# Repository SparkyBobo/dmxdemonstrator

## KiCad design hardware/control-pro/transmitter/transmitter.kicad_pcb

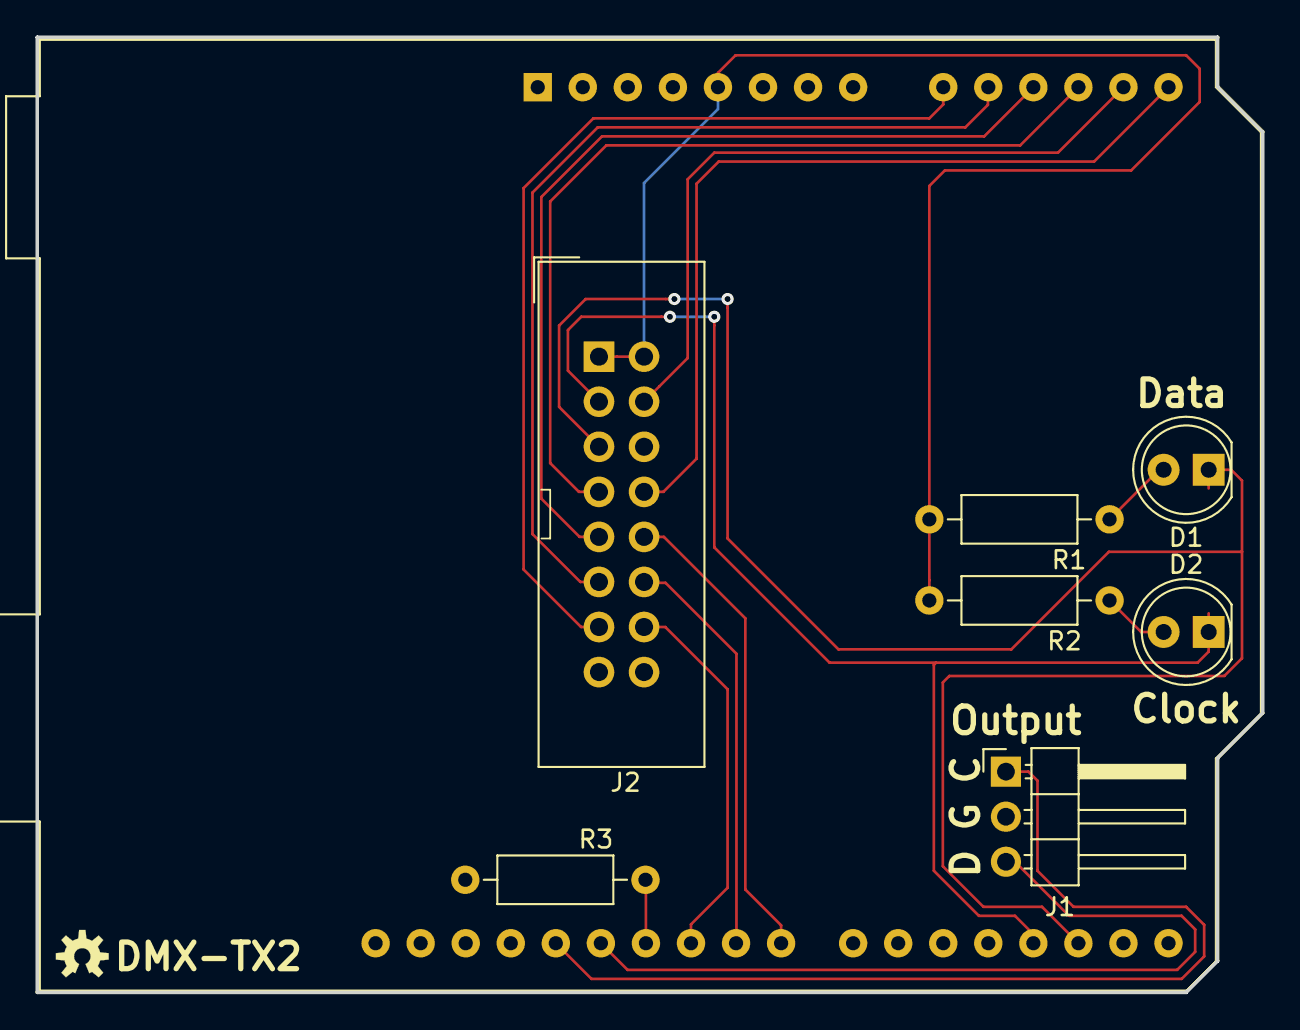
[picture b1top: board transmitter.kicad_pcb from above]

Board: 2 copper layers, 69.1 x 53.8 mm, 8 parts (0 on the bottom side), 18 nets.

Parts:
A1: Arduino_UNO_R3
D1: DATA; LED_D5.0mm
D2: CLOCK; LED_D5.0mm
J1: Output; PinHeader_1x03_P2.54mm_Horizontal
J2: INPUT; IDC-Header_2x08_P2.54mm_Vertical
R1, R2, R3: 330; R_Axial_DIN0207_L6.3mm_D2.5mm_P10.16mm_Horizontal

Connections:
+5V: A1.5, J2.1, J2.2, R1.1, R2.1
/A0: A1.9, J2.13
/A1: A1.10, J2.11
/A2: A1.11, J2.9
/A3: A1.12, J2.7
/A4: A1.13, J2.4
/A5: A1.14, J2.8
/RX: A1.27, J1.3
/RXCLK: A1.28, J1.1
/~CLK_FST: A1.24, J2.12
/~CLK_SLO: A1.23, J2.10
/~CLOCK: A1.18, D2.1, J2.3
/~DATA: A1.17, D1.1, J2.5
/~HWD_DT: A1.25, J2.14
GND: A1.6, A1.7, A1.29, J1.2, J2.6, J2.15, J2.16, R3.2
unnamed: A1.26, R3.1
unnamed: D1.2, R1.2
unnamed: D2.2, R2.2

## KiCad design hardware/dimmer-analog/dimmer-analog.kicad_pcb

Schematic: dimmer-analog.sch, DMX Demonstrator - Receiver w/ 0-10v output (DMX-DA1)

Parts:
A1: Arduino_UNO_R3
C1, C2, C3, C4: .01uF; CAP-PTH-2.54
C5: 10uF; CP_Radial_D5.0mm_P2.50mm
D1: DATA; LED_D5.0mm
D2: CLOCK; LED_D5.0mm
D8: 1N5819; D_DO-41_SOD81_P10.16mm_Horizontal
J1: Input; PinHeader_1x03_P2.54mm_Horizontal
J2: DIMMER_B; PhoenixContact_MSTBA_2,5_5-G-5,08_1x05_P5.08mm_Horizontal
J5: 12V_A; BarrelJack_CUI_PJ-063AH_Horizontal
J6: 12V_B; PhoenixContact_MSTBA_2,5_2-G-5,08_1x02_P5.08mm_Horizontal
R1, R2: 330; R_Axial_DIN0207_L6.3mm_D2.5mm_P10.16mm_Horizontal
R7: 390; R_Axial_DIN0207_L6.3mm_D2.5mm_P10.16mm_Horizontal
R8: 2.7k; R_Axial_DIN0207_L6.3mm_D2.5mm_P10.16mm_Horizontal
U1: LM317T; TO-220-3_Horizontal_TabDown; MPN LM317T; Digi-Key_PN 497-1575-5-ND
U2: 74LS164; DIP-14_W7.62mm
U3: TLC7226A; DIP-20_W7.62mm
U4: LM324A; DIP-14_W7.62mm

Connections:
+5V: A1.5, C2.1, C3.1, R1.1, R2.1, U2.1, U2.14, U3.18
+10V: C1.1, C4.1, C5.1, R7.2, U1.2, U3.4, U4.4 (V+)
/A0: A1.9, U3.17
/A1: A1.10, U3.16
/AO0: U3.2, U4.12 (+)
/AO1: U3.1, U4.3 (+)
/AO2: U3.20, U4.5 (+)
/AO3: U3.19, U4.10 (+)
/B: A1.22, U2.2
/CLK: A1.23, U2.8
/RX: A1.27, J1.3
/RXCLK: A1.28, J1.1
/~CLOCK: A1.14, D2.1
/~CLR: A1.24, U2.9
/~DATA: A1.13, D1.1
/~DIM0: A1.26
/~DIM1: A1.25
/~DIM2: A1.21
/~DIM3: A1.20
/~WR: A1.11, U3.15
GND: A1.6, A1.7, A1.29, C1.2, C2.2, C3.2, C4.2, C5.2, J1.2, J2.1, J5.2, J6.1, R8.1, U2.7, U3.3, U3.5, U3.6, U4.11 (V-)
unnamed: D1.2, R1.2
unnamed: D2.2, R2.2
unnamed: D8.1 (K), U1.3
unnamed: D8.2 (A), J5.1, J6.2
unnamed: J2.2, U4.13 (-), U4.14
unnamed: J2.3, U4.1, U4.2 (-)
unnamed: J2.4, U4.6 (-), U4.7
unnamed: J2.5, U4.8, U4.9 (-)
unnamed: R7.1, R8.2, U1.1
unnamed: U2.3, U3.14
unnamed: U2.4, U3.13
unnamed: U2.5, U3.12
unnamed: U2.6, U3.11
unnamed: U2.10, U3.10
unnamed: U2.11, U3.9
unnamed: U2.12, U3.8
unnamed: U2.13, U3.7

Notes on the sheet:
D0-D4 Reserved For DMX Shield

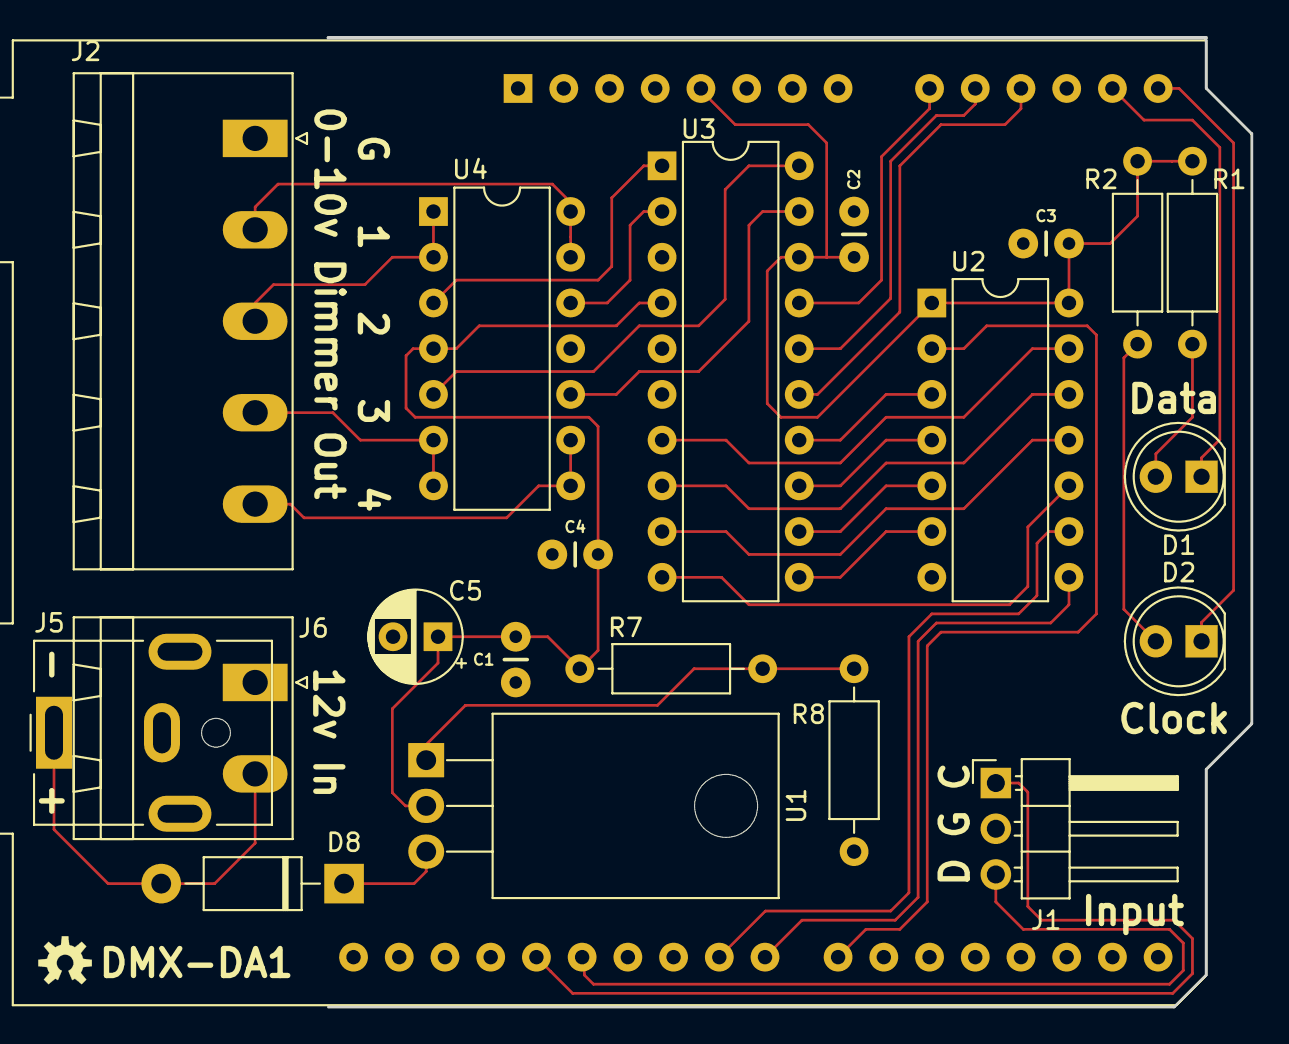
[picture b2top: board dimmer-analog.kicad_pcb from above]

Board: 2 copper layers, 51.3 x 53.8 mm, 21 parts (0 on the bottom side), 34 nets.

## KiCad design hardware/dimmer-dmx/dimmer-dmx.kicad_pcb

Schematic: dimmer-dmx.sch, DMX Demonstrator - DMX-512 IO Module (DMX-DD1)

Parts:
C2, C3, C4, C5: .01uF; CAP-PTH-2.54
J1: IO EXTENSION; IDC-Header_2x07_P2.54mm_Horizontal
J2: NC3FAH/NC5FAH; NEUTRIK-NC3FAH-NC5FAH
J3: NC3MAH/NC5MAH; NEUTRIK-NC3MAH-NC5MAH
MH1, MH2, MH3, MH4: MountingHole; MountingHole_3.2mm_M3
R1: 330; R_Axial_DIN0207_L6.3mm_D2.5mm_P10.16mm_Horizontal
R2, R3, R4, R5, R6, R7: 470; R_Axial_DIN0207_L6.3mm_D2.5mm_P10.16mm_Horizontal
R8, R10: 680; R_Axial_DIN0207_L6.3mm_D2.5mm_P10.16mm_Horizontal
R9: 120; R_Axial_DIN0207_L6.3mm_D2.5mm_P10.16mm_Horizontal
U1: NMA0505SC; Converter_DCDC_muRata_NMAxxxxSC_THT_Bypass
U2, U3, U4: 6N137; DIP-8_W7.62mm_Socket; MPN 6N137; Digi-Key_PN 160-1791-ND
U5: MAX3485CPA+; DIP-8_W7.62mm_Socket

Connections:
+5V: C2.1, J1.1, J1.2, R2.1, U1.1 (VIN+), U2.8, U3.2, U4.2
GND: C2.2, J1.13, J1.14, R1.1, U1.2 (VIN-), U2.5
GNDD: C3.2, C4.2, C5.2, J2.1A, J2.1B, J3.1A, J3.1B, R10.2, U1.4 (VOUT-), U3.5, U4.5, U5.5 (GND)
unnamed: J1.9, R2.2, U2.6
unnamed: J1.10, R4.2
unnamed: J1.11, R6.2
unnamed: J1.12, R1.2
unnamed: J2.2A, J2.2B, J3.2A, J3.2B, R9.1, R10.1, U5.7 (B)
unnamed: J2.3, J3.3, R8.1, R9.2, U5.6 (A)
unnamed: R3.1, U5.1 (RO)
unnamed: R3.2, U2.3
unnamed: R4.1, U3.3
unnamed: R5.1, U3.6, U5.2 (~RE), U5.3 (DE)
unnamed: R6.1, U4.3
unnamed: R7.1, U4.6, U5.4 (DI)
VDD: C3.1, C4.1, C5.1, R5.2, R7.2, R8.2, U1.6 (VOUT+), U2.2, U3.8, U4.8, U5.8 (VCC)

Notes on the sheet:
Connect pin 3 to 6 to bypass isolator
Connect J4 to J5 to bypass isolator
Connect pin 2 to 4 to bypass isolator

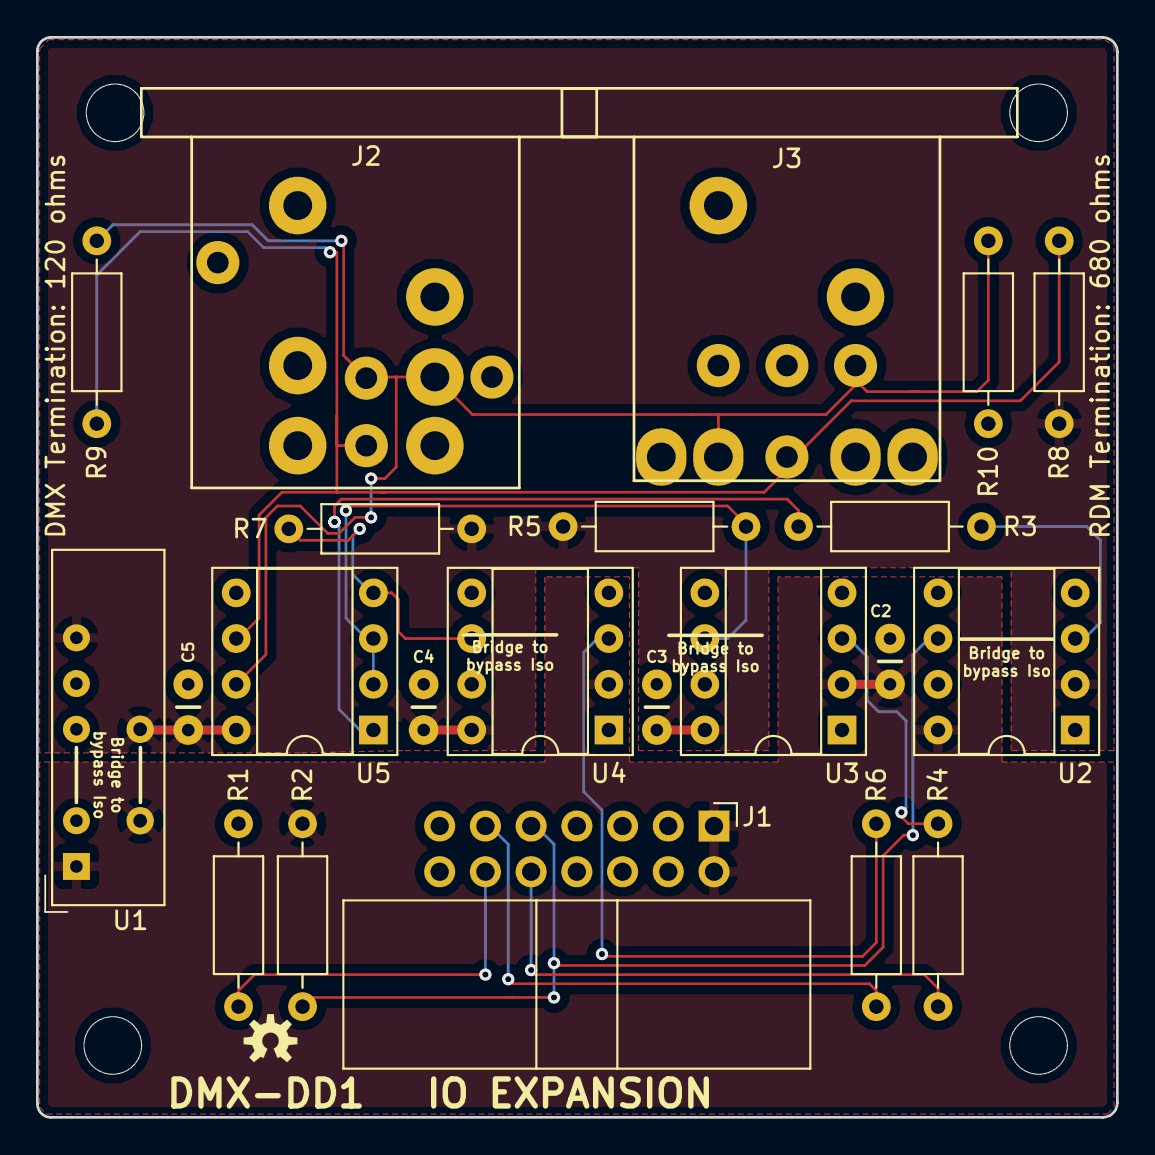
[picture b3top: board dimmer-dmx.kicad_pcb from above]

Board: 2 copper layers, 60.0 x 60.0 mm, 26 parts (0 on the bottom side), 16 nets.

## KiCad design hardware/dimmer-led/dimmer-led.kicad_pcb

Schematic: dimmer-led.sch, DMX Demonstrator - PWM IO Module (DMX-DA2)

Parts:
C1, C2, C3, C4: .01uF; CAP-PTH-2.54
C5: 10uF; CP_Radial_D5.0mm_P2.50mm
C6, C8, C9: 10nf; CAP-PTH-2.54
C7: 100nf; CAP-PTH-2.54
D8: 1N5819; D_DO-41_SOD81_P10.16mm_Horizontal
J1: IO EXTENSION; IDC-Header_2x07_P2.54mm_Horizontal
J2: PWM_OUT; PhoenixContact_MSTBA_2,5_5-G-5,08_1x05_P5.08mm_Horizontal
J5: 12V_A; BarrelJack_CUI_PJ-063AH_Horizontal
J6: 12V_B; PhoenixContact_MSTBA_2,5_2-G-5,08_1x02_P5.08mm_Horizontal
MH1, MH2, MH3, MH4: MountingHole; MountingHole_3.2mm_M3
R1: 10k; R_Axial_DIN0207_L6.3mm_D2.5mm_P10.16mm_Horizontal
R2, R3: 1k; R_Axial_DIN0207_L6.3mm_D2.5mm_P10.16mm_Horizontal
R7: 390; R_Axial_DIN0207_L6.3mm_D2.5mm_P10.16mm_Horizontal
R8: 2.7k; R_Axial_DIN0207_L6.3mm_D2.5mm_P10.16mm_Horizontal
U1: LM317T; TO-220-3_Horizontal_TabDown; MPN LM317T; Digi-Key_PN 497-1575-5-ND
U2: 74LS164; DIP-14_W7.62mm
U3: TLC7226A; DIP-20_W7.62mm
U4: LM339; DIP-14_W7.62mm
U5: LM555; DIP-8_W7.62mm

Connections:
+5V: C2.1, C3.1, J1.1, J1.2, U2.1, U2.14, U3.18
+10V: C1.1, C4.1, C5.1, R7.2, U1.2, U3.4, U4.3 (V+), U5.4, U5.8
/A0: J1.5, U3.17
/A1: J1.7, U3.16
/AO0: U3.2, U4.9 (+)
/AO1: U3.1, U4.5 (+)
/AO2: U3.20, U4.7 (+)
/AO3: U3.19, U4.11 (+)
/~WR: J1.3, U3.15
GND: C1.2, C2.2, C3.2, C4.2, C5.2, C6.1, C7.1, C8.2, C9.2, J1.13, J1.14, J2.1, J5.2, J6.1, R8.1, U2.7, U3.3, U3.5, U3.6, U4.12 (V-), U5.1
unnamed: C6.2, U5.2
unnamed: C7.2, U5.5
unnamed: C8.1, R2.1, R3.2
unnamed: C9.1, R3.1, U4.4 (-), U4.6 (-), U4.8 (-), U4.10 (-)
unnamed: D8.1 (K), U1.3
unnamed: D8.2 (A), J5.1, J6.2
unnamed: J1.4, U2.2
unnamed: J1.6, U2.8
unnamed: J1.8, U2.9
unnamed: J2.2, U4.14
unnamed: J2.3, U4.2
unnamed: J2.4, U4.1
unnamed: J2.5, U4.13
unnamed: R1.1, U5.6
unnamed: R1.2, R2.2, U5.3
unnamed: R7.1, R8.2, U1.1
unnamed: U2.3, U3.14
unnamed: U2.4, U3.13
unnamed: U2.5, U3.12
unnamed: U2.6, U3.11
unnamed: U2.10, U3.10
unnamed: U2.11, U3.9
unnamed: U2.12, U3.8
unnamed: U2.13, U3.7

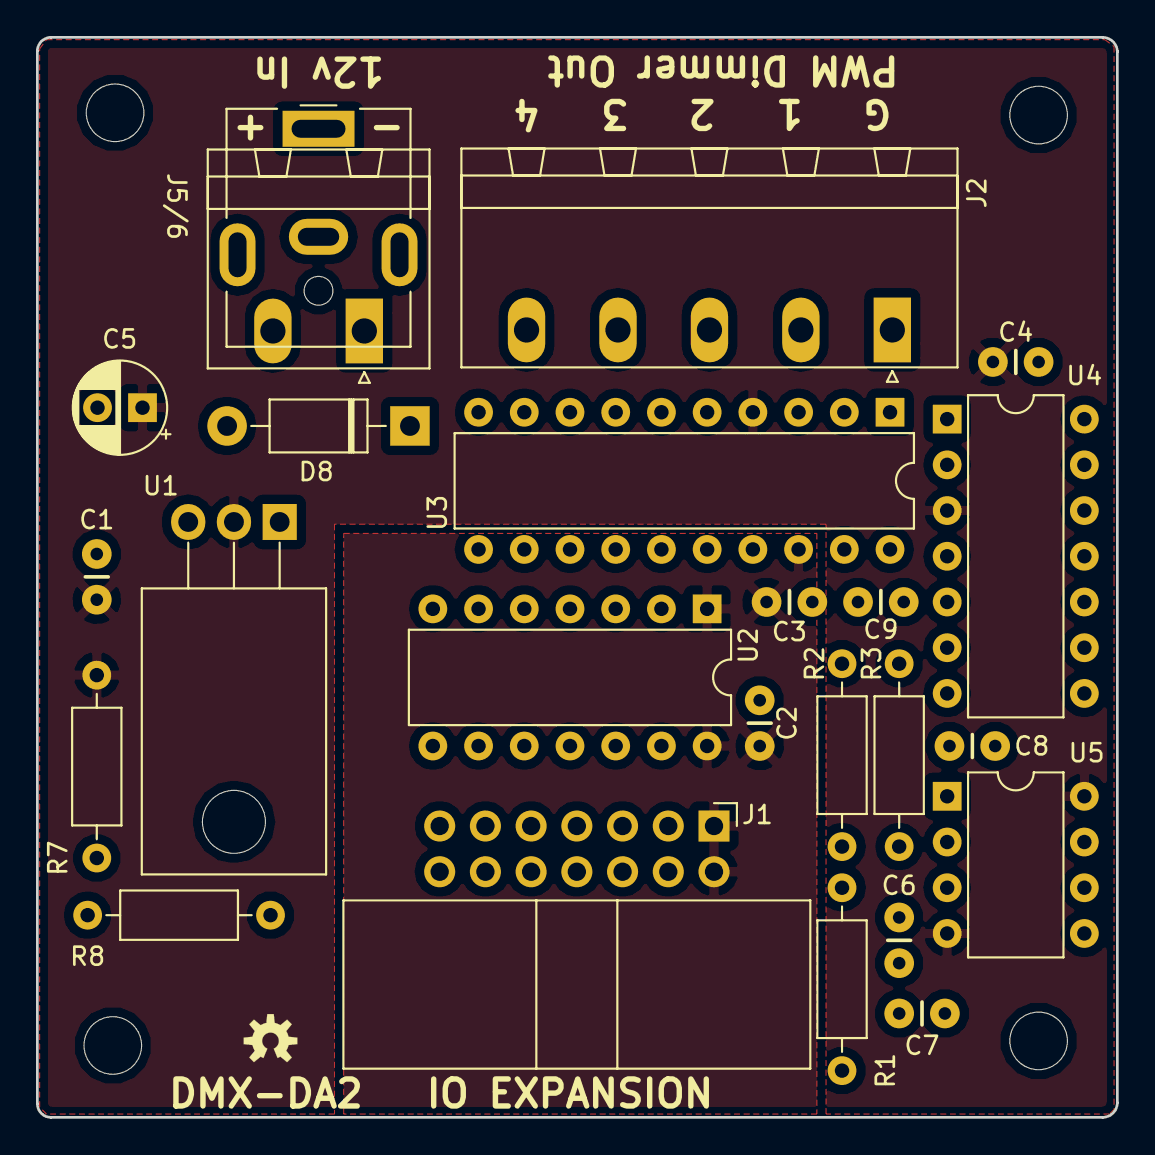
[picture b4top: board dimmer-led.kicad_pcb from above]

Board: 2 copper layers, 60.0 x 60.0 mm, 28 parts (0 on the bottom side), 34 nets, no tracks yet.

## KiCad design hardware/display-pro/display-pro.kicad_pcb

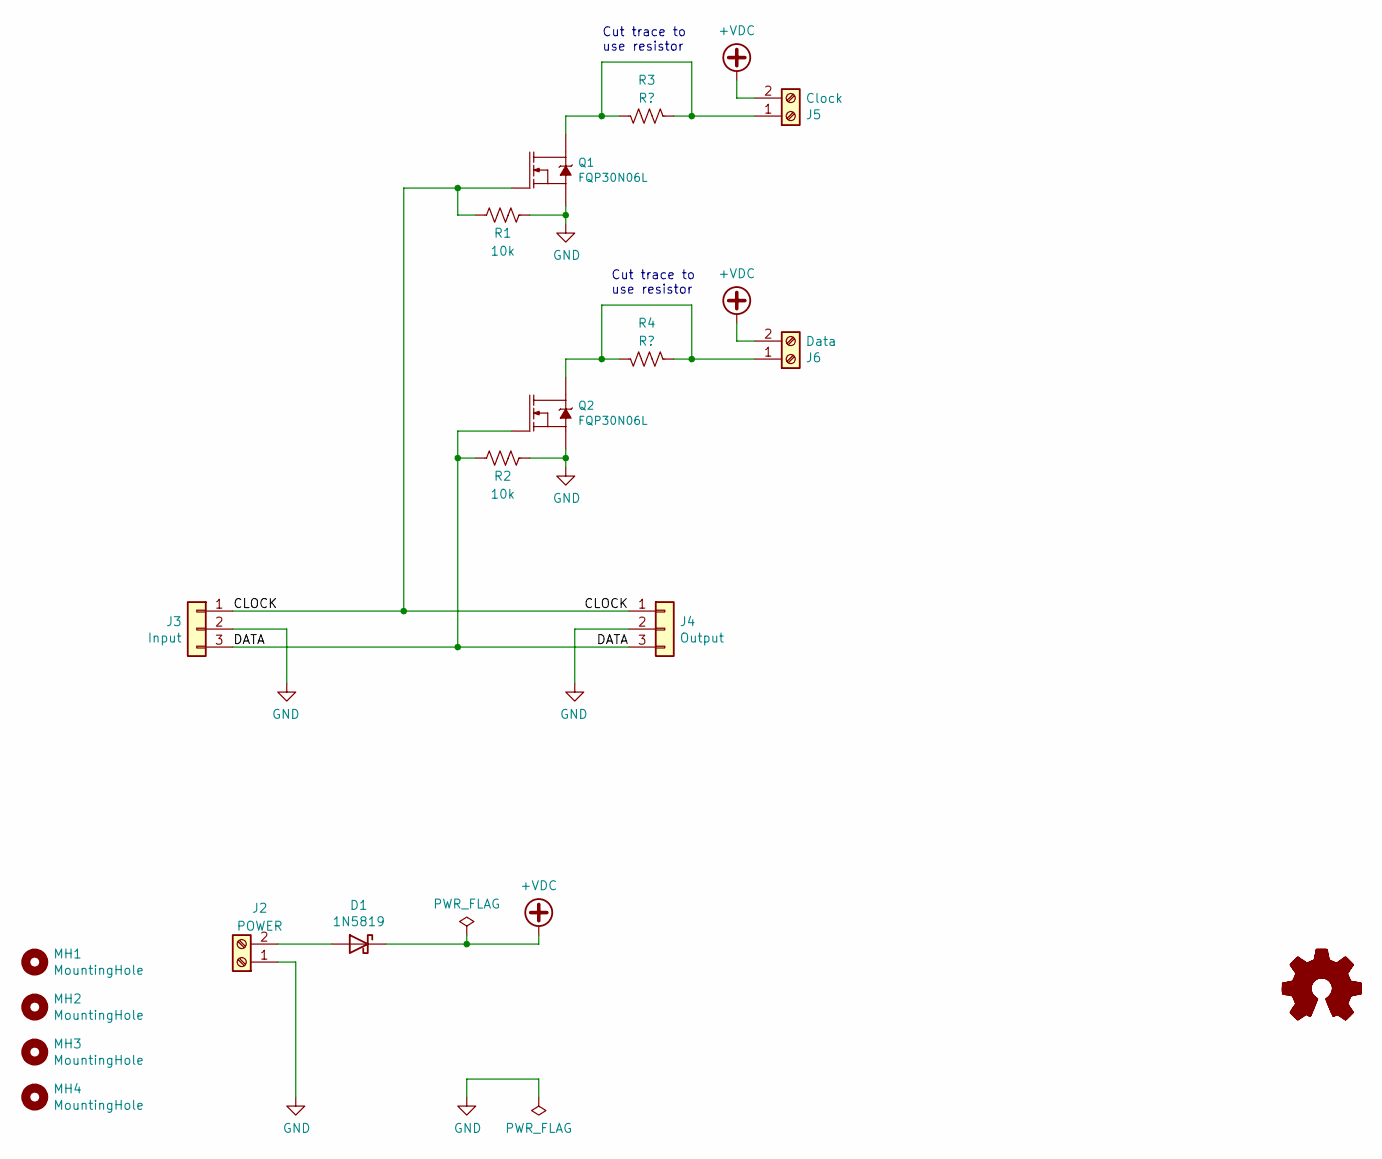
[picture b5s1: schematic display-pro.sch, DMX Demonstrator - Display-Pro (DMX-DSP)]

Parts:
D1: 1N5819; D_DO-41_SOD81_P10.16mm_Horizontal
J2: POWER; PhoenixContact_MSTBA_2,5_2-G-5,08_1x02_P5.08mm_Horizontal
J3: Input; PinHeader_1x03_P2.54mm_Horizontal
J4: Output; PinHeader_1x03_P2.54mm_Horizontal
J5: Clock; PhoenixContact_MSTBA_2,5_2-G-5,08_1x02_P5.08mm_Horizontal
J6: Data; PhoenixContact_MSTBA_2,5_2-G-5,08_1x02_P5.08mm_Horizontal
MH1, MH2, MH3, MH4: MountingHole; MountingHole_3.2mm_M3
Q1, Q2: FQP30N06L; TO-220-3_Horizontal_TabDown
R1, R2: 10k; R_Axial_DIN0207_L6.3mm_D2.5mm_P10.16mm_Horizontal
R3, R4: R?; R_Axial_DIN0411_L9.9mm_D3.6mm_P15.24mm_Horizontal

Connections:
+VDC: D1.1 (K), J5.2, J6.2
/CLOCK: J3.1, J4.1, Q1.1 (G), R1.2
/DATA: J3.3, J4.3, Q2.1 (G), R2.2
GND: J2.1, J3.2, J4.2, Q1.3 (S), Q2.3 (S), R1.1, R2.1
unnamed: D1.2 (A), J2.2
unnamed: J5.1, Q1.2 (D), R3.1, R3.2
unnamed: J6.1, Q2.2 (D), R4.1, R4.2

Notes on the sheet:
Cut trace to use resistor

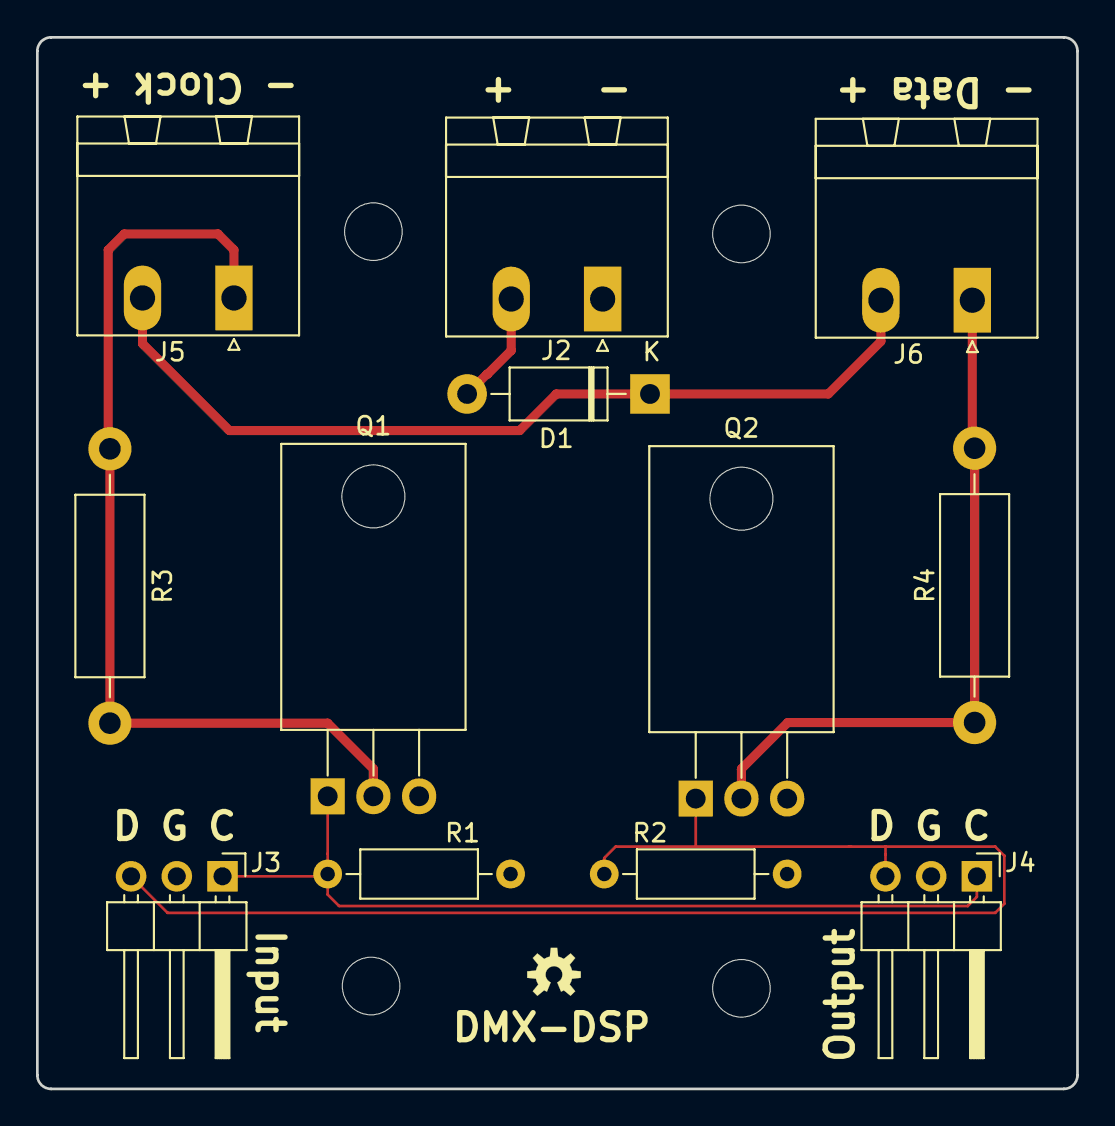
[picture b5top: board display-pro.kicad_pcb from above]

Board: 2 copper layers, 57.8 x 58.4 mm, 16 parts (0 on the bottom side), 7 nets.

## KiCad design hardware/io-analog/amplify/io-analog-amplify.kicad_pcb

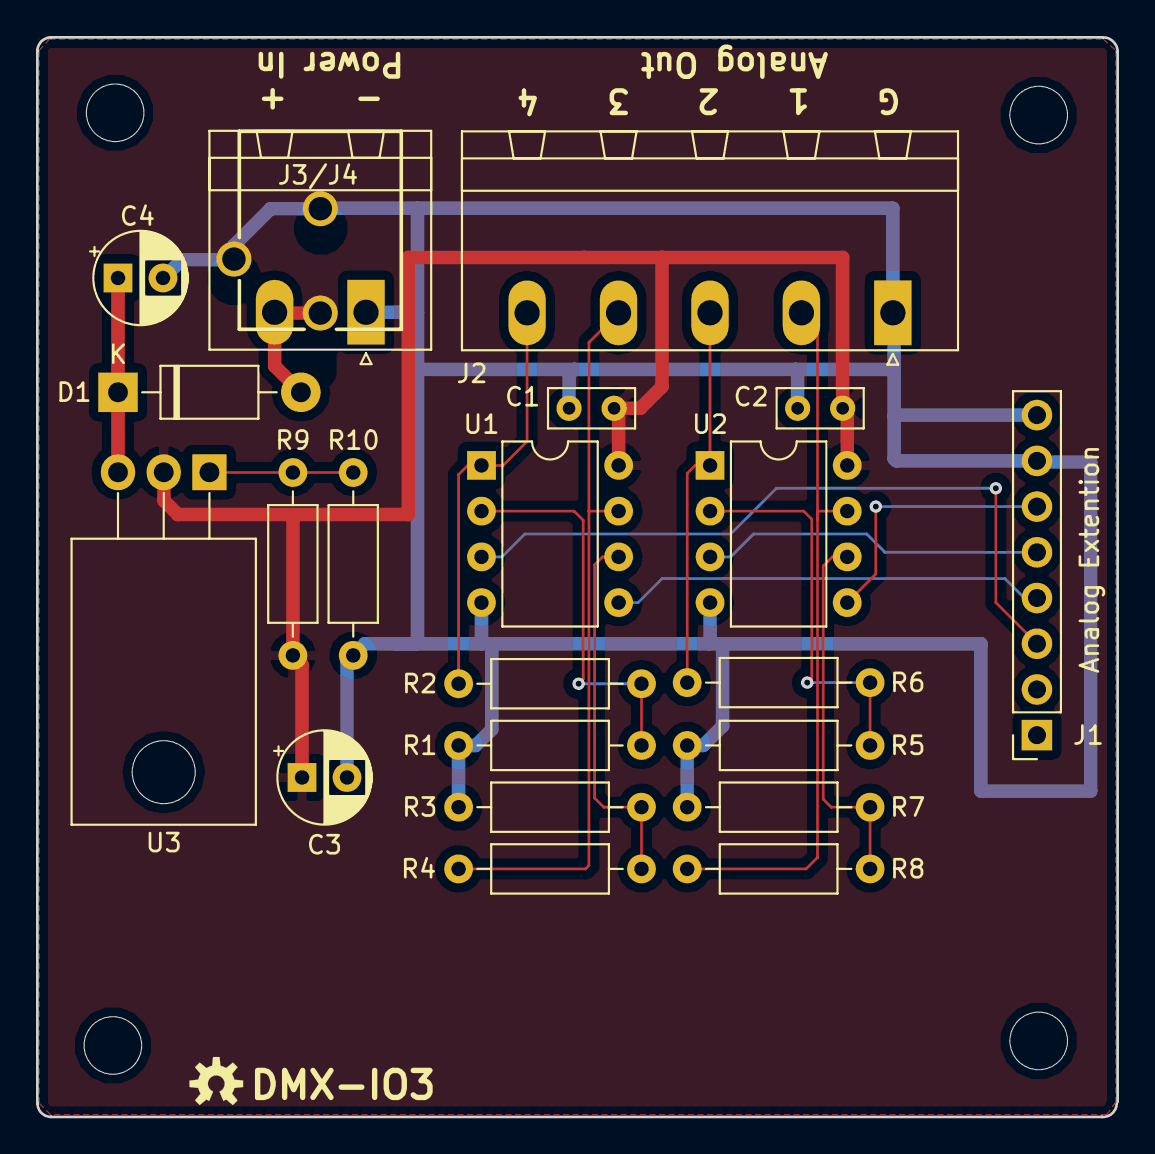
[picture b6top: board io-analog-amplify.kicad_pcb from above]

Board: 2 copper layers, 60.0 x 60.0 mm, 26 parts (0 on the bottom side), 17 nets.

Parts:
C1, C2: 0.1uF; C_Rect_L4.6mm_W2.0mm_P2.50mm_MKS02_FKP02
C3, C4: 10uF; CP_Radial_D5.0mm_P2.50mm
D1: 1N5819; D_DO-41_SOD81_P10.16mm_Horizontal
J1: Analog Extension; PinSocket_1x08_P2.54mm_Vertical
J2: Output; PhoenixContact_MSTBA_2,5_5-G-5,08_1x05_P5.08mm_Horizontal
J3: Power; PhoenixContact_MSTBA_2,5_2-G-5,08_1x02_P5.08mm_Horizontal
J4: Power; POWER_JACK_PTH_BREAD
MH1, MH2, MH3, MH4: MountingHole; MountingHole_3.2mm_M3
R1, R3, R5, R7: 22.6k 1%; R_Axial_DIN0207_L6.3mm_D2.5mm_P10.16mm_Horizontal
R2, R4, R6, R8: 68.1k 1%; R_Axial_DIN0207_L6.3mm_D2.5mm_P10.16mm_Horizontal
R9: 392 1%; R_Axial_DIN0207_L6.3mm_D2.5mm_P10.16mm_Horizontal
R10: 2.74k 1%; R_Axial_DIN0207_L6.3mm_D2.5mm_P10.16mm_Horizontal
U1, U2: TLV2772; DIP-8_W7.62mm
U3: LM317T; TO-220-3_Horizontal_TabDown

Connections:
/AO0: J1.6, U2.5
/AO1: J1.5, U2.3
/AO2: J1.4, U1.5
/AO3: J1.3, U1.3
GND: C1.2, C2.2, C3.2, C4.2, J1.7, J1.8, J2.1, J3.1, J4.GND, J4.GNDB, R1.1, R3.1, R5.1, R7.1, R10.1, U1.4, U2.4
unnamed: C1.1, C2.1, C3.1, R9.2, U1.8, U2.8, U3.2
unnamed: C4.1, D1.1, U3.3
unnamed: D1.2, J3.2, J4.PWR
unnamed: J2.2, R8.2, U2.7
unnamed: J2.3, R6.2, U2.1
unnamed: J2.4, R4.2, U1.7
unnamed: J2.5, R2.1, U1.1
unnamed: R1.2, R2.2, U1.2
unnamed: R3.2, R4.1, U1.6
unnamed: R5.2, R6.1, U2.2
unnamed: R7.2, R8.1, U2.6
unnamed: R9.1, R10.2, U3.1

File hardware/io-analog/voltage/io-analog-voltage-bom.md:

# Bill Of Materials (BOM)

## Schematic

**Filename:** E:\OpenSource\dmxdemonstrator\hardware\io-analog\voltage\io-analog-voltage.sch

**Date Modified:** 8/20/2023 10:47:27 PM

**Kicad Version:** Eeschema (5.0.0)

**Component Count:** 26

## Parts

Reference|Quantity|Value|Part|Datasheet|Vendor(s)
---------|--------|-----|----|---------|------
C1, C2|2|0.1uF|Decoupling Capacitor|~|[Mouser 80-C320C104K5R7301](https://www.mouser.com/ProductDetail/KEMET/C320C104K5R5TA730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, [Newark 13K6284](https://www.newark.com/kemet/c315c104m5u5ta/capacitor-mlcc-z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, [Sparkfun COM-08375](https://www.sparkfun.com/products/8375), [Adafruit 753](https://www.adafruit.com/product/753)
C3, C4|2|10uF|Filter Capacitor|~|[Digikey P10425CT-ND](https://www.digikey.com/en/products/detail/panasonic-electro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, [Mouser 667-ECA-1HM100I](https://www.mouser.com/ProductDetail/Panasonic/ECA-1HM100I), [Newark ECA-1HM100I](), [Sparkfun COM-00523](https://www.sparkfun.com/products/523), [Adafruit 2195](https://www.adafruit.com/product/2195)
D1|1|1N5819|Reverse Voltage Protection|[Data Sheet](http://www.vishay.com/docs/88525/1n5817.pdf)|[Digikey 1N5819-E3/54GITR-ND](https://www.digikey.com/en/products/detail/vishay-general-se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, [Mouser 625-1N5819-E3](https://www.mouser.com/ProductDetail/Vishay-General-Semicond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, [Newark 78K2616](https://www.newark.com/vishay/1n5819-e3-54/schottky-rectifie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, [Sparkfun COM-10926](https://www.sparkfun.com/products/10926)
J1|1|Analog Extension|Arduino Stackable Header - 8 Pin|~|[Mouser 992-8FX1L-254MM](https://www.mouser.com/ProductDetail/Gravitech/8Fx1L-254mm?q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, [Sparkfun PRT-09279](https://www.sparkfun.com/products/9279)
J2|1|Output|Screw Terminal|~|[Digikey 277-1109-ND](https://www.digikey.com/en/products/detail/phoenix-contact/1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, [Mouser 651-1757271](https://www.mouser.com/ProductDetail/Phoenix-Contact/1757271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
J3|1|Power|Screw Terminal|~|[Digikey 277-1106-ND](https://www.digikey.com/en/products/detail/phoenix-contact/1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, [Mouser 651-1757242](https://www.mouser.com/ProductDetail/Phoenix-Contact/1757242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
J4|1|Power|DC Barrel Jack|[Data Sheet](https://www.sparkfun.com/products/10811)|[Sparkfun CONN-08197](https://www.sparkfun.com/products/10811)
R1, R3, R5, R7|4|22.6k 1%||~|[Digikey 22.6KXBK-ND](https://www.digikey.com/en/products/detail/yageo/MFR-25FBF52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, [Mouser 603-MFR-25FBF52-22K6](https://www.mouser.com/ProductDetail/YAGEO/MFR-25FBF52-22K6?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
R2, R4, R6, R8|4|68.1k 1%||~|[Digikey 68.1KXBK-ND](https://www.digikey.com/en/products/detail/yageo/MFR-25FBF52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, [Mouser 603-MFR-25FBF52-68K1](https://www.mouser.com/ProductDetail/YAGEO/MFR-25FBF52-68K1?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
R9|1|392 1%||~|[Digikey 392XBK-ND](https://www.digikey.com/en/products/detail/yageo/MFR-25FBF52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, [Mouser 603-MFR-25FBF52-392R](https://www.mouser.com/ProductDetail/YAGEO/MFR-25FBF52-392R?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
R10|1|2.74k 1%||~|[Digikey 13-MFR-25FRF52-2K74TR-ND](https://www.digikey.com/en/products/detail/yageo/MFR-25FRF52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, [Mouser 603-MFR-25FRF52-2K74](https://www.mouser.com/ProductDetail/YAGEO/MFR-25FRF52-2K74?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
U1, U2|2|TLV2772|Rail-to-Rail Operational Amplifier|[Data Sheet](https://www.ti.com/lit/ds/slos209g/slos209g.pdf)|[Digikey 296-7592-5-ND](https://www.digikey.com/en/products/detail/texas-instruments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, [Mouser TLV2772CP](https://www.mouser.com/ProductDetail/Texas-Instruments/TLV27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
U3|1|LM317T|IC REG LIN POS ADJ 1.5A TO220AB|[Data Sheet](http://www.st.com/content/ccc/resource/technical/document/da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|[Digikey 497-1575-5-ND](https://www.digikey.com//product-detail/en/stmicroelectronic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, [Mouser 511-LM317T](https://www.mouser.com/ProductDetail/STMicroelectronics/LM31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

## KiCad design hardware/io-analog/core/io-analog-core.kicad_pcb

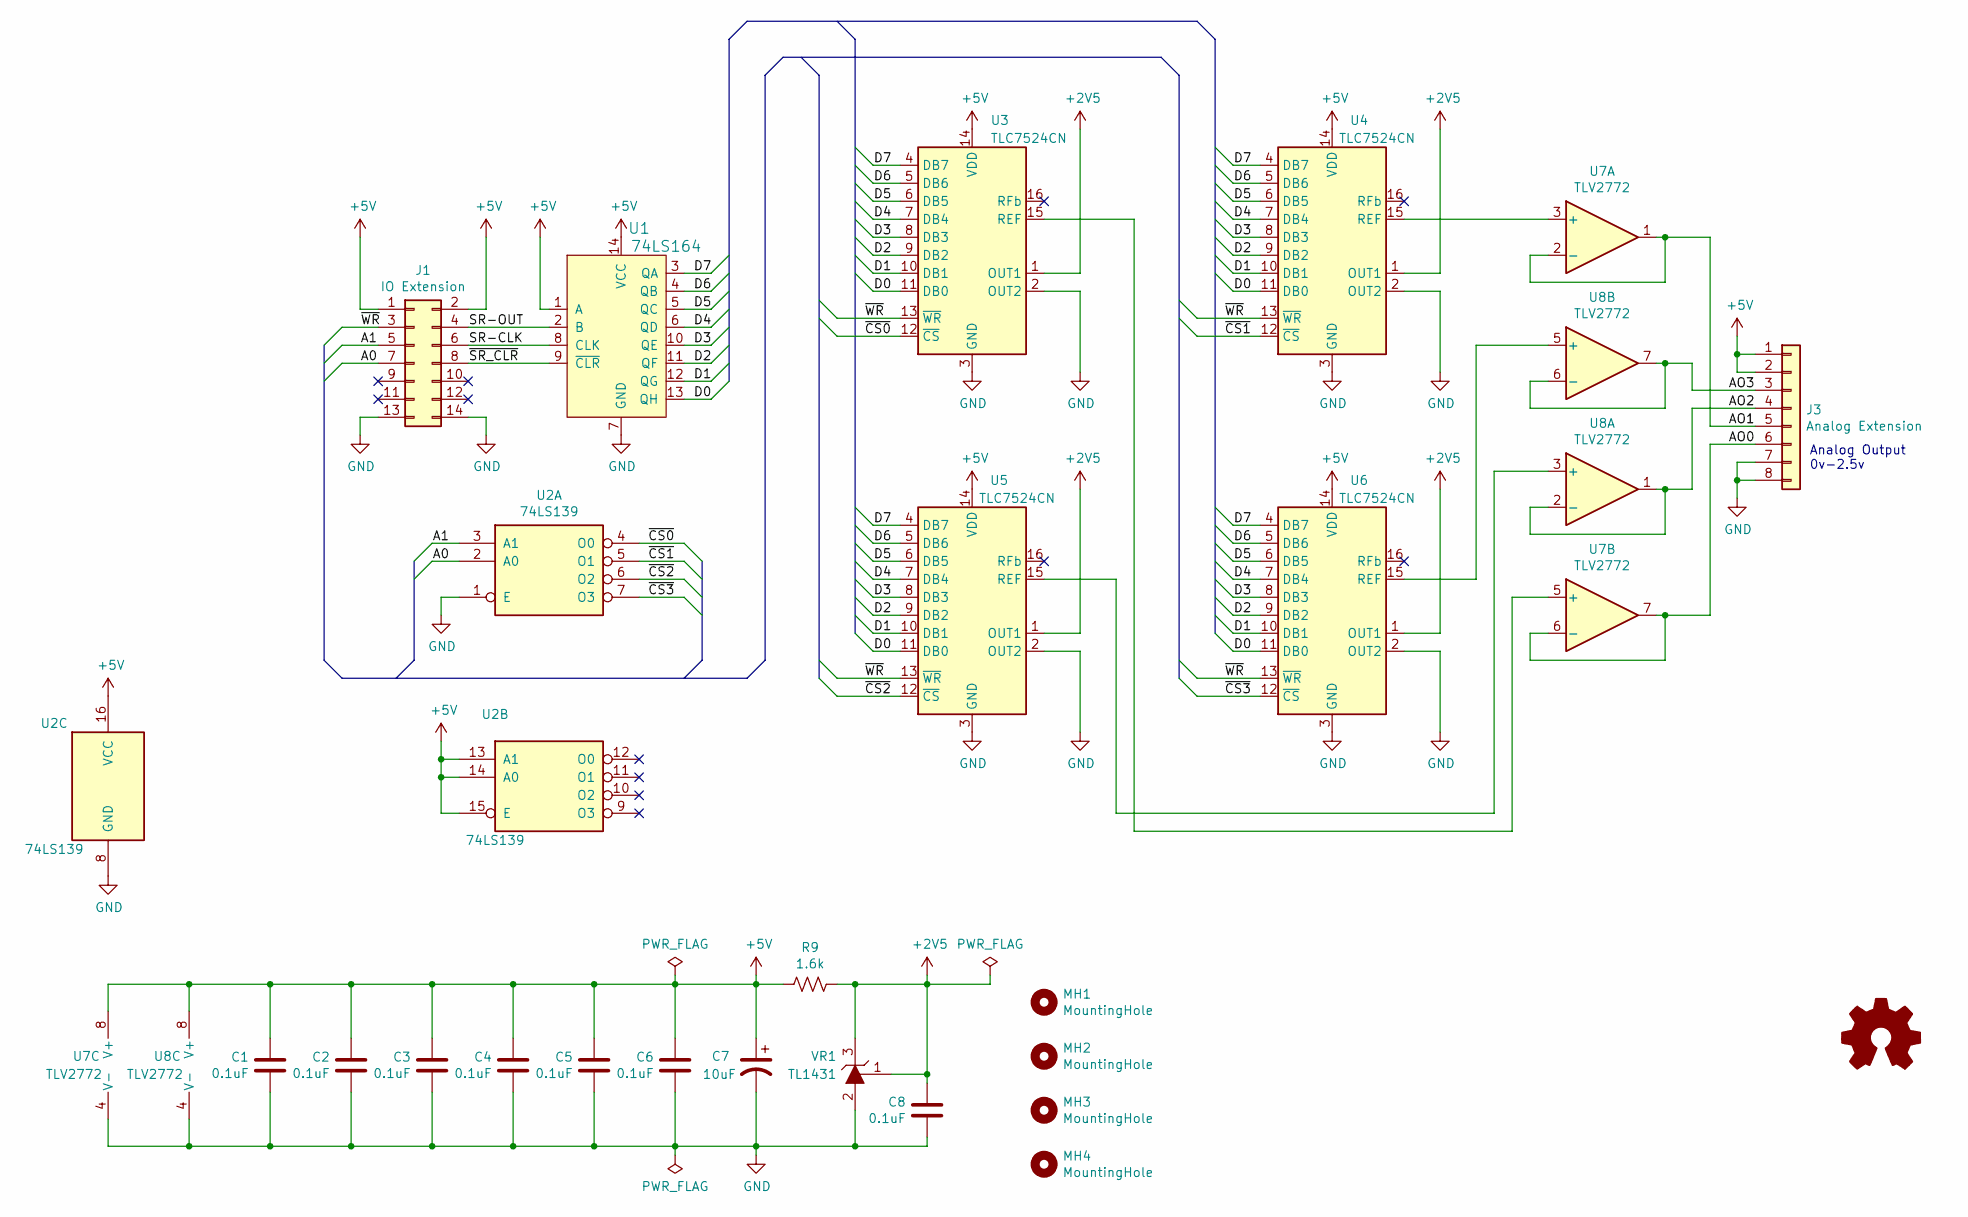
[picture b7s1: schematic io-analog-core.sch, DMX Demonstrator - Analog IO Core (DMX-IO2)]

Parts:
C1, C2, C3, C4, C5, C6, C8: 0.1uF; C_Rect_L4.6mm_W2.0mm_P2.50mm_MKS02_FKP02
C7: 10uF; CP_Radial_D4.0mm_P1.50mm; Digi-Key_PN P10425CT-ND
J1: IO Extension; IDC-Header_2x07_P2.54mm_Horizontal; Digi-Key_PN 732-5407-ND
J3: Analog Extension; PinHeader_1x08_P2.54mm_Vertical
MH1, MH2, MH3, MH4: MountingHole; MountingHole_3.2mm_M3
R9: 1.6k; R_Axial_DIN0207_L6.3mm_D2.5mm_P10.16mm_Horizontal; Digi-Key_PN 1.6KQBK-ND
U1: 74LS164; DIP-14_W7.62mm; Digi-Key_PN 296-1647-5-ND
U2: 74LS139; DIP-16_W7.62mm; Digi-Key_PN 296-1640-5-ND
U3, U4, U5, U6: TLC7524CN; DIP-16_W7.62mm; Digi-Key_PN 296-1868-5-ND
U7: TLV2772; DIP-8_W7.62mm; Digi-Key_PN 296-7592-5-ND
U8: TLV2772; DIP-8_W7.62mm
VR1: TL1431; TO-92_Inline_Wide; Digi-Key_PN 296-10130-5-ND

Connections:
+2V5: C8.1, R9.1, U3.1 (OUT1), U4.1 (OUT1), U5.1 (OUT1), U6.1 (OUT1), VR1.1 (REF), VR1.3 (K)
+5V: C1.1, C2.1, C3.1, C4.1, C5.1, C6.1, C7.1, J1.1, J1.2, J3.1, J3.2, R9.2, U1.1 (A), U1.14 (VCC), U2.13 (A1), U2.14 (A0), U2.15 (E), U2.16 (VCC), U3.14 (VDD), U4.14 (VDD), U5.14 (VDD), U6.14 (VDD), U7.8 (V+), U8.8 (V+)
/A0: J1.7, U2.2 (A0)
/A1: J1.5, U2.3 (A1)
/AO0: J3.6, U7.6 (-), U7.7
/AO1: J3.5, U7.1, U7.2 (-)
/AO2: J3.4, U8.1, U8.2 (-)
/AO3: J3.3, U8.6 (-), U8.7
/D0: U1.13 (QH), U3.11 (DB0), U4.11 (DB0), U5.11 (DB0), U6.11 (DB0)
/D1: U1.12 (QG), U3.10 (DB1), U4.10 (DB1), U5.10 (DB1), U6.10 (DB1)
/D2: U1.11 (QF), U3.9 (DB2), U4.9 (DB2), U5.9 (DB2), U6.9 (DB2)
/D3: U1.10 (QE), U3.8 (DB3), U4.8 (DB3), U5.8 (DB3), U6.8 (DB3)
/D4: U1.6 (QD), U3.7 (DB4), U4.7 (DB4), U5.7 (DB4), U6.7 (DB4)
/D5: U1.5 (QC), U3.6 (DB5), U4.6 (DB5), U5.6 (DB5), U6.6 (DB5)
/D6: U1.4 (QB), U3.5 (DB6), U4.5 (DB6), U5.5 (DB6), U6.5 (DB6)
/D7: U1.3 (QA), U3.4 (DB7), U4.4 (DB7), U5.4 (DB7), U6.4 (DB7)
/SR-CLK: J1.6, U1.8 (CLK)
/SR-OUT: J1.4, U1.2 (B)
/~CS0: U2.4 (O0), U3.12 (~CS)
/~CS1: U2.5 (O1), U4.12 (~CS)
/~CS2: U2.6 (O2), U5.12 (~CS)
/~CS3: U2.7 (O3), U6.12 (~CS)
/~SR_CLR: J1.8, U1.9 (~CLR)
/~WR: J1.3, U3.13 (~WR), U4.13 (~WR), U5.13 (~WR), U6.13 (~WR)
GND: C1.2, C2.2, C3.2, C4.2, C5.2, C6.2, C7.2, C8.2, J1.13, J1.14, J3.7, J3.8, U1.7 (GND), U2.1 (E), U2.8 (GND), U3.2 (OUT2), U3.3 (GND), U4.2 (OUT2), U4.3 (GND), U5.2 (OUT2), U5.3 (GND), U6.2 (OUT2), U6.3 (GND), U7.4 (V-), U8.4 (V-), VR1.2 (A)
unnamed: U3.15 (REF), U7.5 (+)
unnamed: U4.15 (REF), U7.3 (+)
unnamed: U5.15 (REF), U8.3 (+)
unnamed: U6.15 (REF), U8.5 (+)

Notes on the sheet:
Analog Output 0v-2.5v

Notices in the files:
hardware/control-pro/transmitter/transmitter.kicad_pcb:
https://creativecommons.org/licenses/by-sa/4.0
Released under the Creative Commons Attribution Share-Alike 4.0 License
hardware/dimmer-analog/dimmer-analog.kicad_pcb:
Released under the Creative Commons Attribution Share-Alike 4.0m License
